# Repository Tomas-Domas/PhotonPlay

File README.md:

# PhotonPlay
Galvonometer scanner display for retro games

## Implemented Features
Galvanometer
- DAC and amplified bipolar signal circuit is built and tested.
- Digilent DA2 control signal generation script and workspace file.

FPGA
- Integrated LUT on BRAM.
- Parallel to serial converter that uses a handshake protocol to talk to DAC.
- HDL module for transmitting LUT values to DAC through PMOD interface.

Known Issues / Bugs
- Op-amps are not properly working as rail-to-rail amplifiers, limiting the range of voltages output to the galvanometer driver circuit.
- HDL modules not fully parameterized for re-use.
- LUT generation script not yet able to generate binary files for more compact HDL code.

## Vivado Instructions:
We'll be programming the the Pynq-Z2 board using Vivado, follow Dr Stitt's setup guide for Lab0:
http://www.gstitt.ece.ufl.edu/courses/fall24/eel4720_5721/labs/

I use Vivado 2021.1 and have had no issues but newer versions are probably also fine.

## Adding the Pnyq-Z2 board to Vivado:
Once Vivado is installed, you'll need to add the Pynq-Z2 board to your setup. You can follow the instructions here:
https://community.element14.com/technologies/fpga-group/b/blog/posts/add-pynq-z2-board-to-vivado

Create a board_files folder inside the boards directory if you don't already have one. To check if the process worked create a Vivado project and keep all the defults selected until you reach the Defualt Part screen. Select the boards tab and search Pynq-Z2. The board should appear like so:

## Port Mapping the board:
Port mapping boards are generally done using an .xdc file. Download the Master XDC file using the Tul website:
https://www.tulembedded.com/FPGA/ProductsPYNQ-Z2.html#:~:text=Z2%20Board%20File

Inside the extracted download you'll see a tcl and xdc file. The video below walks you through making an example project with the Pynq-Z2 board and how to use the tcl and xdc file to interface with it:
https://youtu.be/AG15wnyXWaA

Around the 1:36 mark I run the command:
get_property CONFIG.XXXX [get_bd_cells processing_system7_0]

Go into the tcl file and test running this command on random settings like the CONFIG.PCW_DDR_RAM_BASEADDR. This command should return the value given in the tcl file (for instance if running CONFIG.PCW_DDR_RAM_BASEADDR it should return 0x00100000). If this command returns an value that does not align with the tcl file then something went awry. Finally add the xdc file to constraints. The xdc file is currently how pin mapping will be done.

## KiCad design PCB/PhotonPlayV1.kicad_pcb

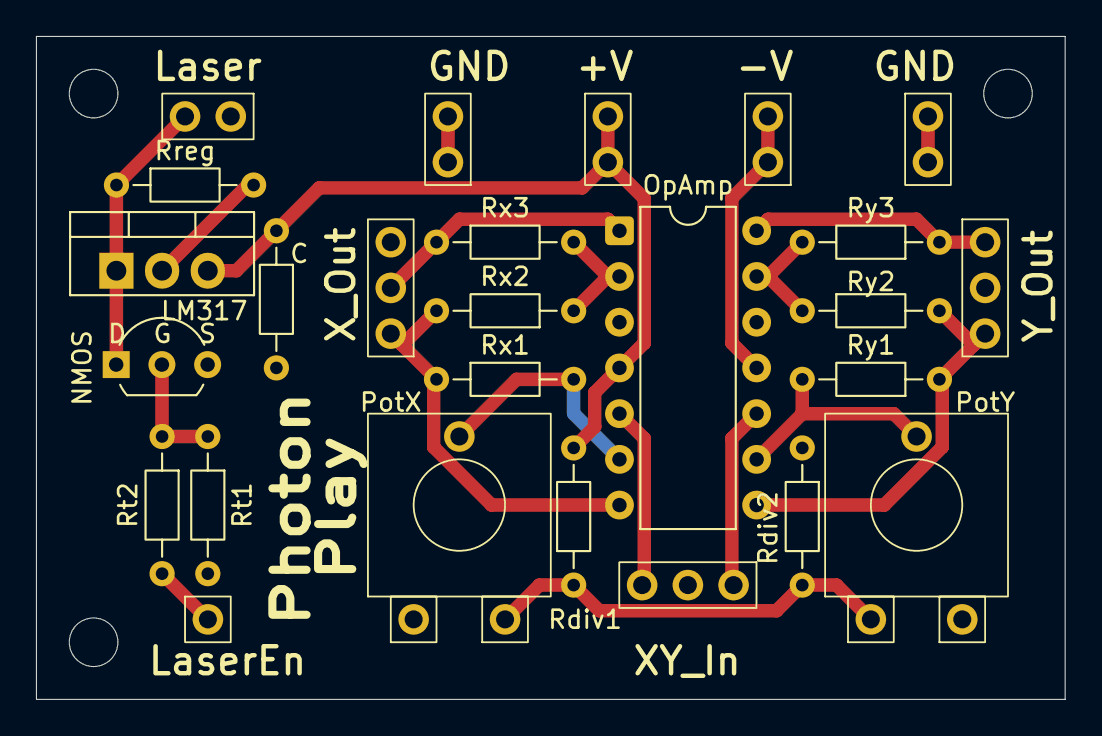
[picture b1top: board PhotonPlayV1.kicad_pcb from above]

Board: 2 copper layers, 57.1 x 36.8 mm, 29 parts (0 on the bottom side), 18 nets.

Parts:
${VALUE}: Rreg; R_Axial_DIN0204_L3.6mm_D1.6mm_P7.62mm_Horizontal
${VALUE}#2: OpAmp; DIP-14_W7.62mm
${VALUE}#3: NMOS; TO-92L_Inline_Wide
+15V1: +15V; PhotonPlay_Header01x02
-15V1: -15V; PhotonPlay_Header01x02
C: C_Small; R_Axial_DIN0204_L3.6mm_D1.6mm_P7.62mm_Horizontal
GND1, GND2: GND; PhotonPlay_Header01x02
H1, H2, H3: MountingHole; MountingHole_2.7mm
LM317: LM317_TO-220; TO-220-3_Vertical
Laser1: Laser; PhotonPlay_Header01x02
LaserEn1: LaserEn; PhotonPlay_Header01x01
PotX1: PotX; PhotonPlay_Potentiometer
PotY1: PotY; PhotonPlay_Potentiometer
Rdiv1: 22k; R_Axial_DIN0204_L3.6mm_D1.6mm_P7.62mm_Horizontal
Rdiv2: 10k; R_Axial_DIN0204_L3.6mm_D1.6mm_P7.62mm_Horizontal
Rt1: 100; R_Axial_DIN0204_L3.6mm_D1.6mm_P7.62mm_Horizontal
Rt2: 10k; R_Axial_DIN0204_L3.6mm_D1.6mm_P7.62mm_Horizontal
Rx1: 4.7k; R_Axial_DIN0204_L3.6mm_D1.6mm_P7.62mm_Horizontal
Rx2, Rx3: 10k; R_Axial_DIN0204_L3.6mm_D1.6mm_P7.62mm_Horizontal
Ry1: 4.7k; R_Axial_DIN0204_L3.6mm_D1.6mm_P7.62mm_Horizontal
Ry2, Ry3: 10k; R_Axial_DIN0204_L3.6mm_D1.6mm_P7.62mm_Horizontal
XY_Input1: XY_In; PhotonPlay_Header01x03
X_Output1: X_Out; PhotonPlay_Header01x03
Y_Output1: Y_Out; PhotonPlay_Header01x03

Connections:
+15V: ${VALUE}#2.4 (V+), +15V1.1, +15V1.2, C.1, LM317.3 (VI), Rdiv1.2
/+5V: PotX1.3, PotY1.1, Rdiv1.1, Rdiv2.2
/-15V: ${VALUE}#2.11 (V-), -15V1.1, -15V1.2
/Gate: ${VALUE}#3.2 (G), Rt1.1, Rt2.1
/Vreg: ${VALUE}.1, ${VALUE}#3.1 (D), LM317.1 (ADJ), Laser1.2
/X+: ${VALUE}#2.7, Rx1.1, Rx2.2, X_Output1.1
/X-: ${VALUE}#2.1, Rx3.1, X_Output1.2
/X_In: ${VALUE}#2.5 (+), XY_Input1.3
/Y+: ${VALUE}#2.8, Ry1.1, Ry2.2, Y_Output1.3
/Y-: ${VALUE}#2.14, Ry3.1, Y_Output1.1
/Y_In: ${VALUE}#2.10 (+), XY_Input1.1
GND: ${VALUE}#2.3 (+), ${VALUE}#2.12 (+), ${VALUE}#3.3 (S), C.2, GND1.1, GND1.2, GND2.1, GND2.2, Laser1.1, Rdiv2.1, Rt2.2, XY_Input1.2, X_Output1.3, Y_Output1.2
unnamed: ${VALUE}.2, LM317.2 (VO)
unnamed: LaserEn1.1, Rt1.2
unnamed: ${VALUE}#2.2 (-), Rx2.1, Rx3.2
unnamed: ${VALUE}#2.6 (-), PotX1.2, Rx1.2
unnamed: ${VALUE}#2.9 (-), PotY1.2, Ry1.2
unnamed: ${VALUE}#2.13 (-), Ry2.1, Ry3.2

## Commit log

2025-04-08 Upload LUT generation script
    Add script to generate look-up tables of any function, with custom size and precision.
2025-04-13 Add presentation demo materials
2025-04-16 added vivado code
2025-04-17 Add function for generating verilog lut
2025-04-19 added 2 channel vivado demo
2025-09-04 Update script to take LUT_SIZE in # of entries
2025-09-09 added tb and transformer module
2025-09-09 added two shapes
2025-09-09 added display output recorder to tb
2025-09-09 added tracing tool for output files generated
2025-09-18 Registered position values so they don't change for each point drawn
2025-09-18 Added bound checks and fixed button handling. ~Mylee
2025-09-22 Merged Laser enable into drivers
2025-09-23 Added a clock divider and more points to the triangle, laser_en should now be output from the board. ~Mylee
2025-09-25 Added collision detection between triangle and apple. Apple moves to random spot upon collision. Made things more parameterized, and slight code cleanup. ~Mylee
2025-10-02 moved all tb files into tb directory
2025-10-02 Broken, moves too fast and negative directions don't work. ~Mylee
    Resets to middle of screen upon hitting borders, and combined speed and speed_reg blocks into one
2025-10-05 updated tb
2025-10-06 added more assertions. Segment drawing
2025-10-09 Add KiCad PCB design files
2025-10-09 Update PCB layout with solved clearance issues
2025-10-10 Added self-collision to snake
    Changed the velocity to match the snake body size, so it doesn't constantly collide with itself.
2025-10-12 Make final edits and add generated drill and gerber files
2025-10-23 updated simple tb with btn and laser_en
2025-10-23 added changing length
2025-10-24 Mylee cleaned up code
2025-10-28 restructure
2025-10-30 Add support for reference images
2025-10-30 Add ability to shift all points with arrow keys
2025-10-31 release candid
2025-10-31 added win screen
2025-11-04 Add export function and laser_en toggle to AssetMaker
2025-11-04 added external button support
2025-11-04 fixed last element bug; merged changes
2025-11-04 remerged win
2025-11-04 Add 2nd screen for scaling and positioning asset
2025-11-06 added start state, and ability to leave win state when button pressed
2025-11-06 added randomized apple
2025-11-06 New start screen
2025-11-13 New lut for the win condition
    Test by making max num segments = 3, and draw update speedown = 1750. Reset these values to their original value when done, might need to udjust draw update speedown.
2025-11-13 FIXED BUTTONS HOLY
2025-11-18 added delay for laser_en
2025-11-20 fixed laser enable
2025-11-20 fixed delay and fixed win screen
